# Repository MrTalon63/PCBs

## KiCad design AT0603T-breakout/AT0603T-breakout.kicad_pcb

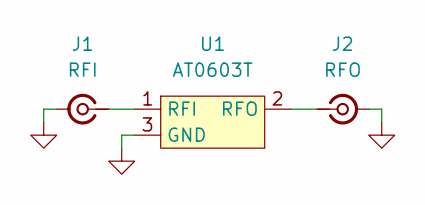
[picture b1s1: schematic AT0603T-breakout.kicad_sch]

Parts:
J1: RFI; SMA_Samtec_SMA-J-P-H-ST-EM1_EdgeMount
J2: RFO; SMA_Samtec_SMA-J-P-H-ST-EM1_EdgeMount
U1: AT0603T

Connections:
GND: J1.2 (Ext), J2.2 (Ext), U1.3 (GND)
unnamed: J1.1 (In), U1.1 (RFI)
unnamed: J2.1 (In), U1.2 (RFO)

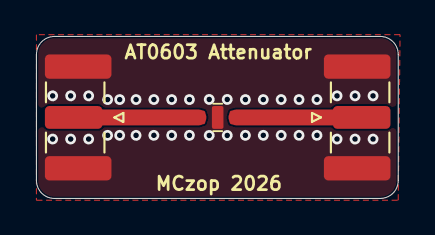
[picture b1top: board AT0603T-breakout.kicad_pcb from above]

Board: 2 copper layers, 20.1 x 9.0 mm, 3 parts (0 on the bottom side), 3 nets.

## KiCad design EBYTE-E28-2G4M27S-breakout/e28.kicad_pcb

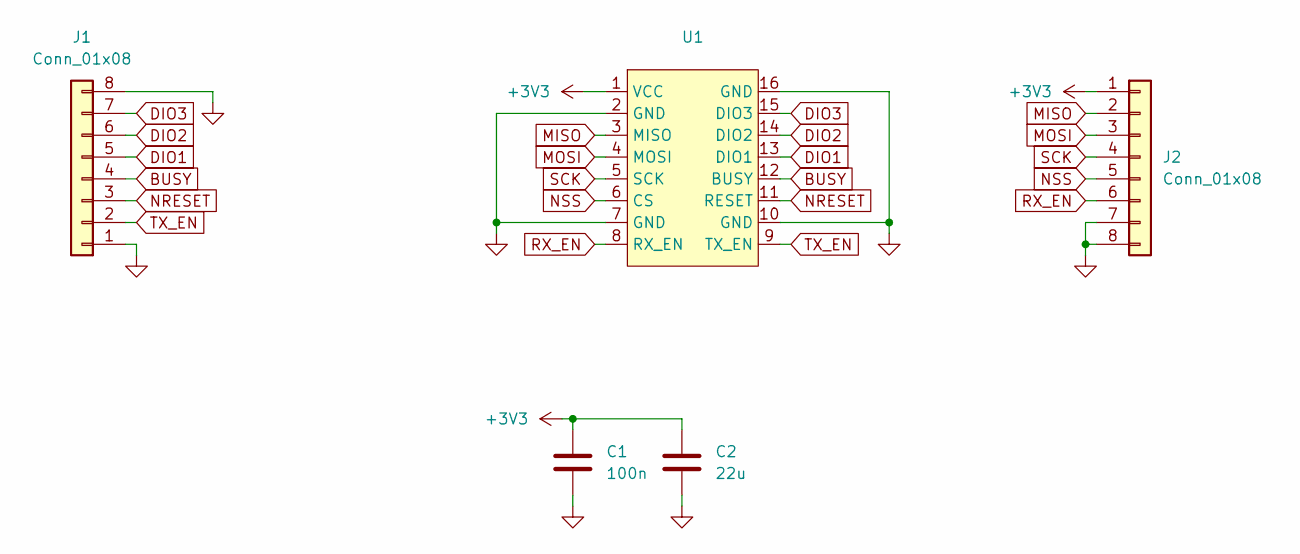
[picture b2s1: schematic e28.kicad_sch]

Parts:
C1: 100n; C_0603_1608Metric_Pad1.08x0.95mm_HandSolder
C2: 22u; C_0603_1608Metric_Pad1.08x0.95mm_HandSolder
J1, J2: Conn_01x08; PinHeader_1x08_P2.54mm_Vertical
U1: E28-2G4M27S

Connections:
+3V3: C1.1, C2.1, J2.1, U1.1 (VCC)
BUSY: J1.4, U1.12 (BUSY)
DIO1: J1.5, U1.13 (DIO1)
DIO2: J1.6, U1.14 (DIO2)
DIO3: J1.7, U1.15 (DIO3)
GND: C1.2, C2.2, J1.1, J1.8, J2.7, J2.8, U1.2 (GND), U1.7 (GND), U1.10 (GND), U1.16 (GND)
MISO: J2.2, U1.3 (MISO)
MOSI: J2.3, U1.4 (MOSI)
NRESET: J1.3, U1.11 (RESET)
NSS: J2.5, U1.6 (CS)
RX_EN: J2.6, U1.8 (RX_EN)
SCK: J2.4, U1.5 (SCK)
TX_EN: J1.2, U1.9 (TX_EN)

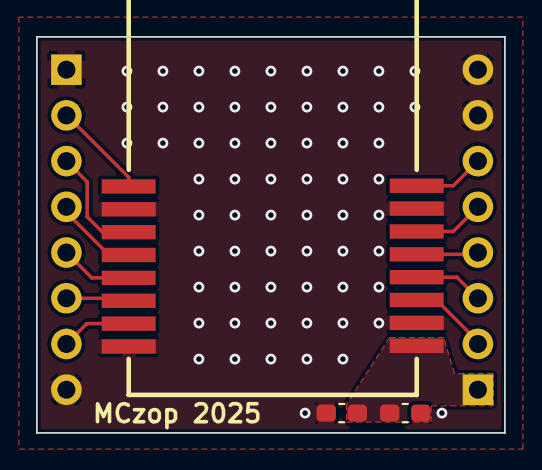
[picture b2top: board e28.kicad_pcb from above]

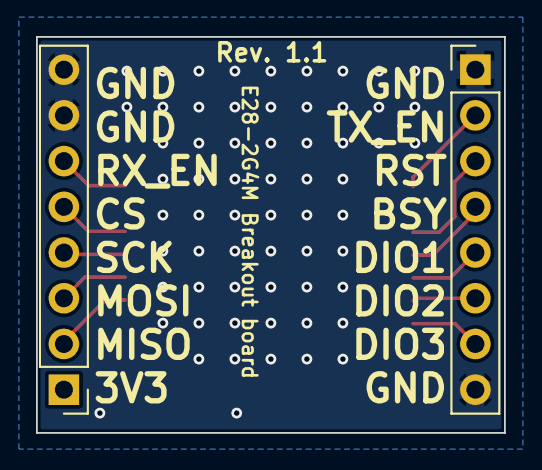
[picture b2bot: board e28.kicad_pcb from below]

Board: 2 copper layers, 26.0 x 22.0 mm, 5 parts (2 on the bottom side), 13 nets.

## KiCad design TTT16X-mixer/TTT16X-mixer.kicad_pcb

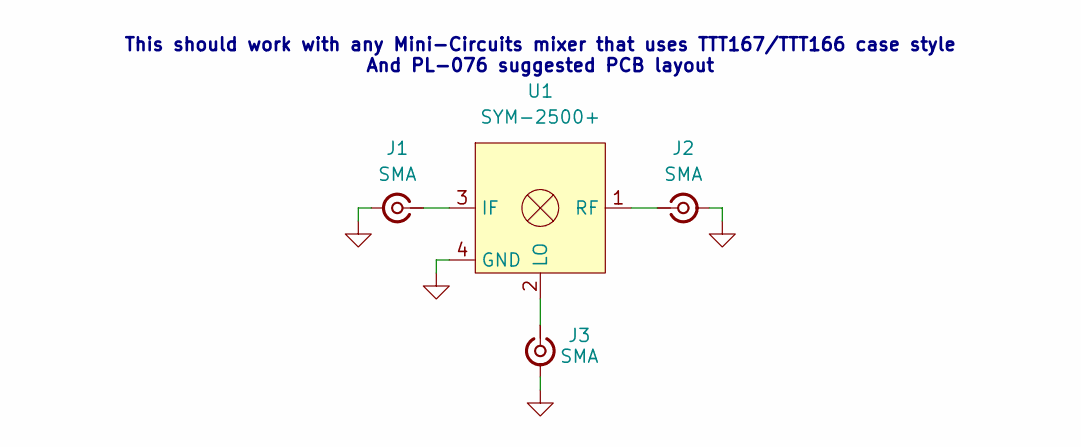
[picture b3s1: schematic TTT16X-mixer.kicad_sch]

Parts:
J1, J2, J3: SMA; SMA_Samtec_SMA-J-P-H-ST-EM1_EdgeMount
U1: SYM-2500+; Mini-Circuits_TTT167_LandPatternPL-079

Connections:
GND: J1.2 (Ext), J2.2 (Ext), J3.2 (Ext), U1.4 (GND)
unnamed: J1.1 (In), U1.3 (IF)
unnamed: J2.1 (In), U1.1 (RF)
unnamed: J3.1 (In), U1.2 (LO)

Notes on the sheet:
This should work with any Mini-Circuits mixer that uses TTT167/TTT166 case style And PL-076 suggested PCB layout

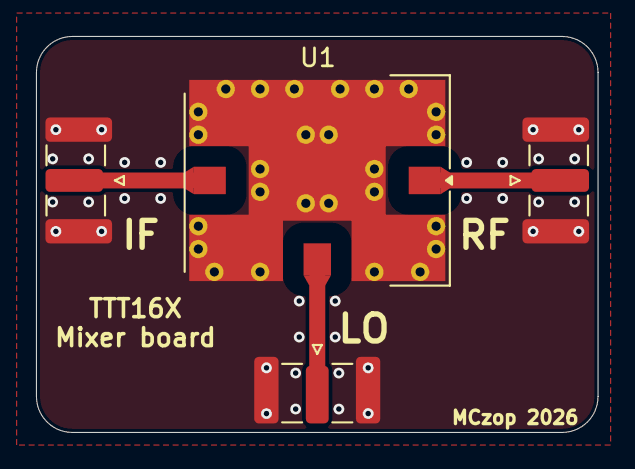
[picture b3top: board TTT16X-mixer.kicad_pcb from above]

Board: 2 copper layers, 31.2 x 22.0 mm, 4 parts (0 on the bottom side), 4 nets.

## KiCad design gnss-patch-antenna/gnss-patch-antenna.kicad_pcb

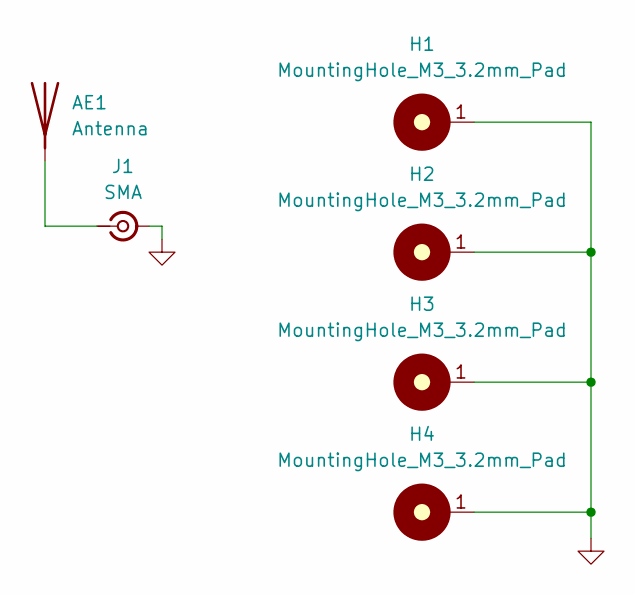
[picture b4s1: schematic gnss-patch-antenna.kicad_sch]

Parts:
AE1: Antenna; Pin_D1.0mm_L10.0mm
H1, H2, H3, H4: MountingHole_M3_3.2mm_Pad; MountingHole_3.2mm_Pad
J1: SMA; SMA_Samtec_SMA-J-P-H-ST-EM1_EdgeMount

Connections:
GND: H1.1, H2.1, H3.1, H4.1, J1.2 (Ext)
unnamed: AE1.1 (A_1), J1.1 (In)

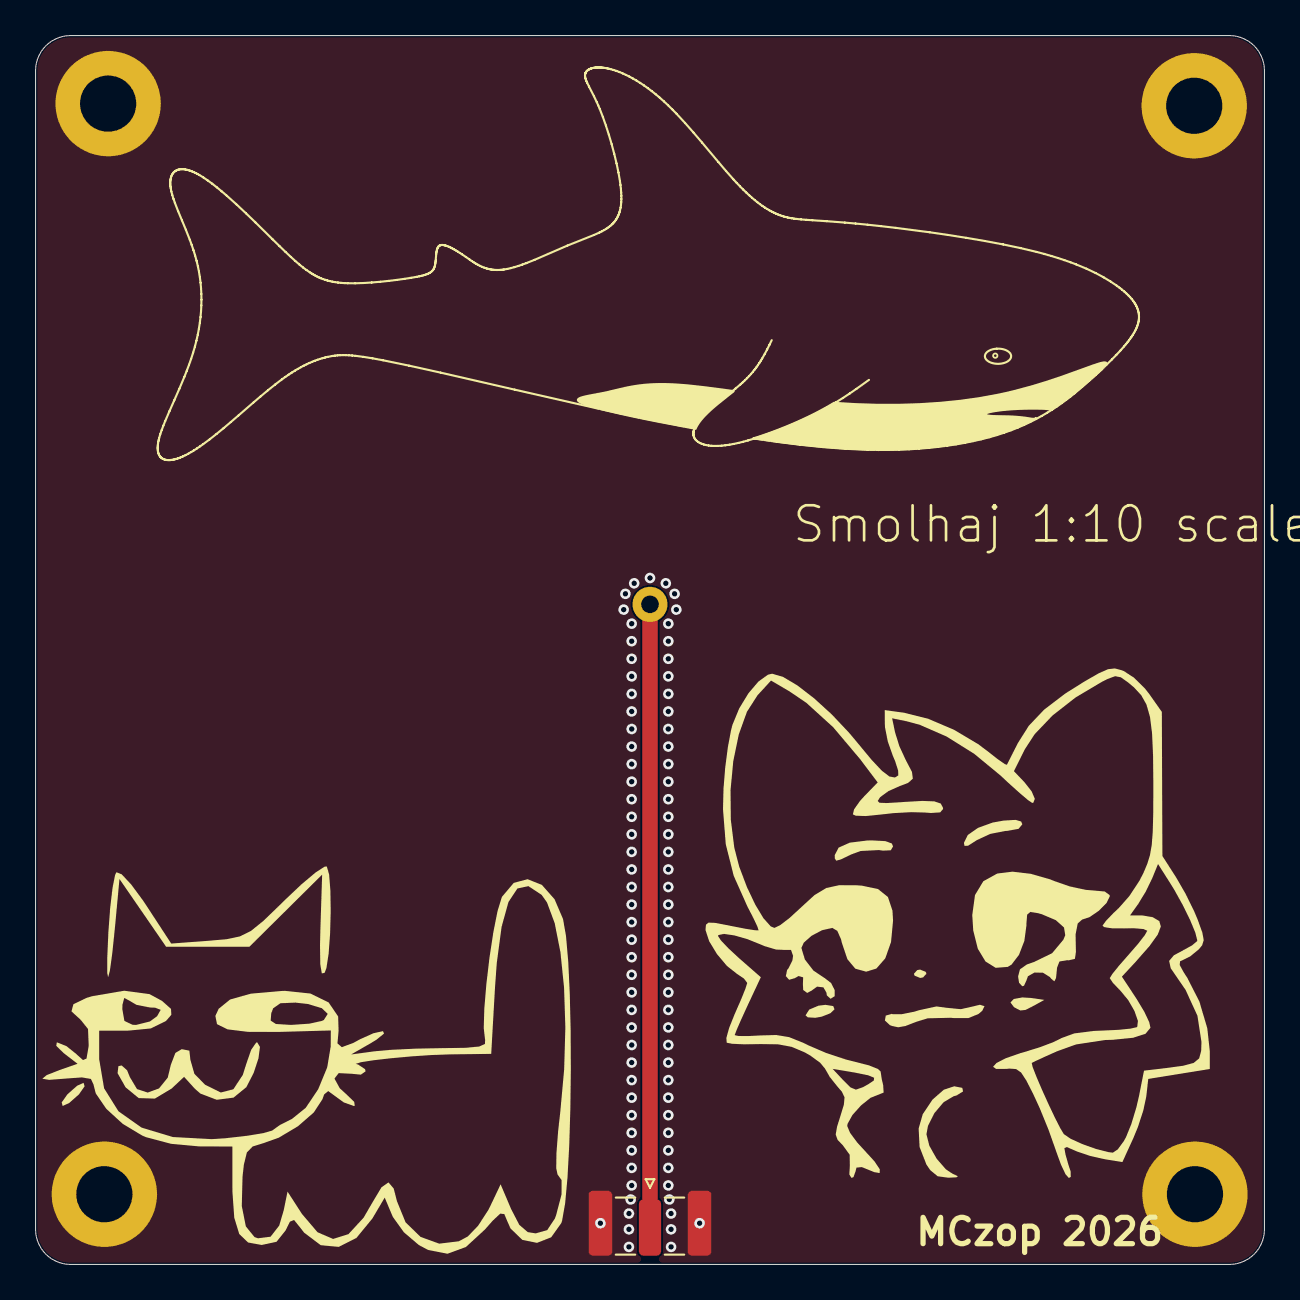
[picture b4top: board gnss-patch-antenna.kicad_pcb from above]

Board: 2 copper layers, 70.0 x 70.0 mm, 6 parts (1 on the bottom side), 2 nets.

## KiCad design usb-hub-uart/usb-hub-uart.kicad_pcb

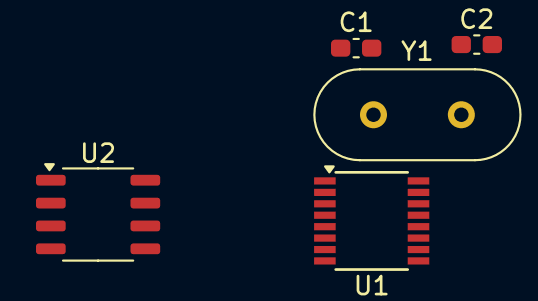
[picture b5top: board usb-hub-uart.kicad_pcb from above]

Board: 2 copper layers, 5 parts (0 on the bottom side), 5 nets, no tracks yet.

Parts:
C1, C2: 15p; C_0603_1608Metric_Pad1.08x0.95mm_HandSolder
U1: SSOP-16_3.9x4.9mm_P0.635mm
U2: CH340N; SOP-8_3.9x4.9mm_P1.27mm
Y1: 12MHz XO; Crystal_HC49-4H_Vertical

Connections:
D1M: U1.7 (DM1), U2.2 (UD-)
D1P: U1.8 (DP1), U2.1 (UD+)
GND: C1.1, C2.1, U1.14 (GND), U2.3 (GND)
unnamed: C2.2, U1.15 (XIN), Y1.2
unnamed: C1.2, U1.16 (XOUT), Y1.1

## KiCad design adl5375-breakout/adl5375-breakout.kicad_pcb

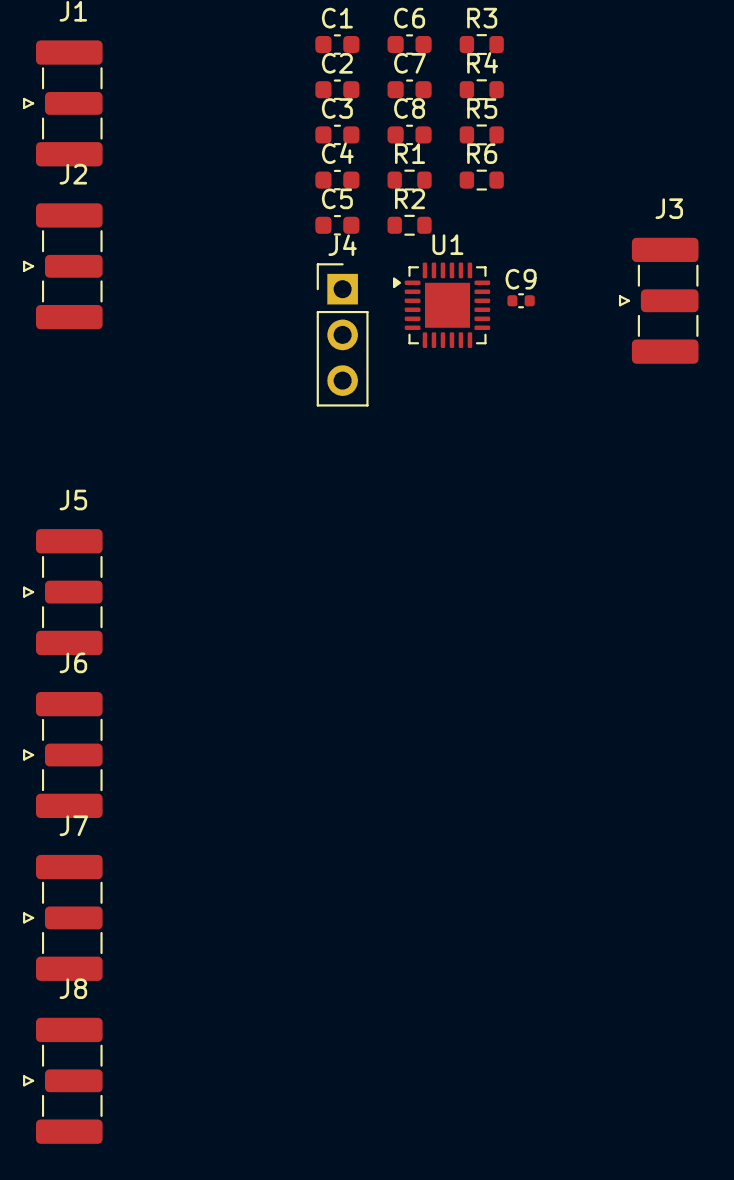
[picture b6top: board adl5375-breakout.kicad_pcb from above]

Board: 2 copper layers, 24 parts (0 on the bottom side), 17 nets, no tracks yet.

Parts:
C1, C2: 100n; C_0603_1608Metric
C3: 1u; C_0603_1608Metric
C4, C5, C6, C7, C8: 100p; C_0603_1608Metric
C9: 100p; C_0402_1005Metric
J1: LOIP; SMA_Samtec_SMA-J-P-H-ST-EM1_EdgeMount
J2: LOIN; SMA_Samtec_SMA-J-P-H-ST-EM1_EdgeMount
J3: RFOUT; SMA_Samtec_SMA-J-P-H-ST-EM1_EdgeMount
J4: DSOP; PinHeader_1x03_P2.54mm_Vertical
J5: IBBN; SMA_Samtec_SMA-J-P-H-ST-EM1_EdgeMount
J6: IBBP; SMA_Samtec_SMA-J-P-H-ST-EM1_EdgeMount
J7: QBBN; SMA_Samtec_SMA-J-P-H-ST-EM1_EdgeMount
J8: QBBP; SMA_Samtec_SMA-J-P-H-ST-EM1_EdgeMount
R1, R2, R3, R4: 0; R_0603_1608Metric
R5, R6: 100; R_0603_1608Metric
U1: ADL5375; LFCSP-24-1EP_4x4mm_P0.5mm_EP2.5x2.5mm

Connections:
+3V3: C1.1, C2.1, C3.1, J4.3, U1.18 (VCC), U1.24 (VCC)
GND: C1.2, C2.2, C3.2, J1.2 (Ext), J2.2 (Ext), J3.2 (Ext), J4.1, J5.2 (Ext), J6.2 (Ext), J7.2 (Ext), J8.2 (Ext), U1.2 (GND), U1.5 (GND), U1.8 (GND), U1.11 (GND), U1.12 (GND), U1.14 (GND), U1.17 (GND), U1.19 (GND), U1.20 (GND), U1.23 (GND), U1.25 (GND)
unnamed: C4.2, C6.1, R2.1
unnamed: C5.2, C6.2, R1.1
unnamed: C7.1, R2.2, R4.1
unnamed: C7.2, R1.2, R3.1
unnamed: C8.1, J1.1 (In), R4.2
unnamed: C8.2, J2.1 (In), R3.2
unnamed: C9.2, J3.1 (In)
unnamed: J4.2, U1.1 (DSOP)
unnamed: J5.1 (In), R5.1, U1.22 (IBBN)
unnamed: J6.1 (In), R5.2, U1.21 (IBBP)
unnamed: J7.1 (In), R6.1, U1.9 (QBBN)
unnamed: J8.1 (In), R6.2, U1.10 (QBBP)
unnamed: C5.1, U1.4 (LOIN)
unnamed: C4.1, U1.3 (LOIP)
unnamed: C9.1, U1.16 (RFOUT)

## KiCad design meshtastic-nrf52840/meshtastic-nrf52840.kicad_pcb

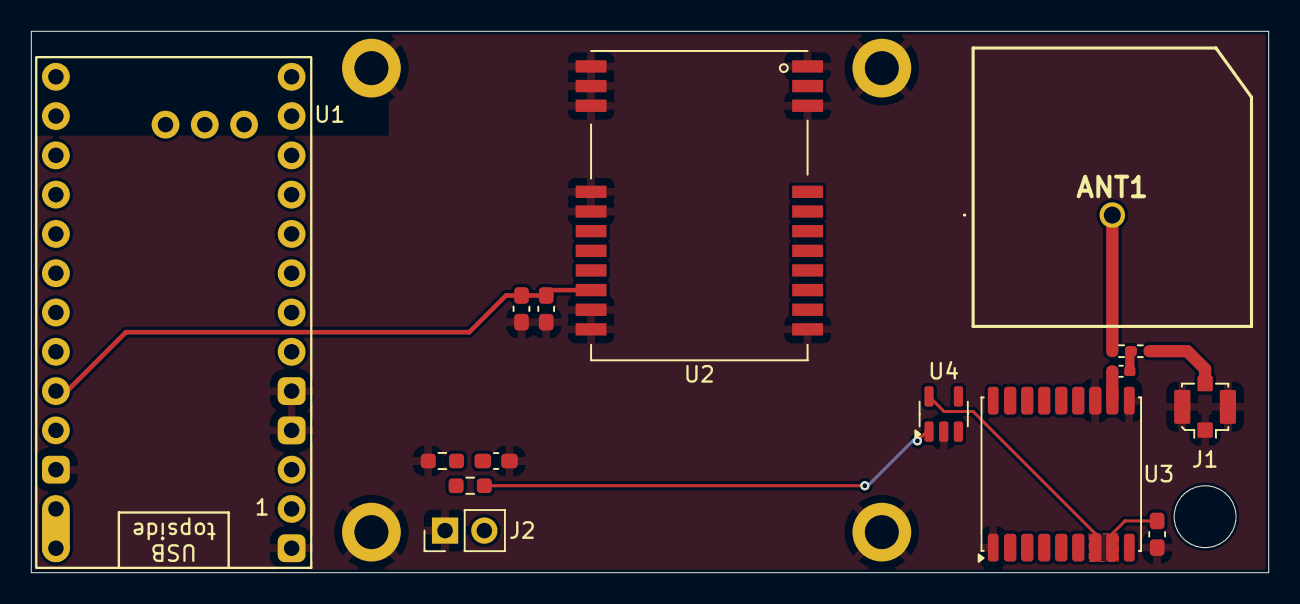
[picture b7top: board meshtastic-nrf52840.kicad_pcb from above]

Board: 2 copper layers, 80.0 x 35.0 mm, 20 parts (0 on the bottom side), 9 nets.

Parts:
ANT1: GPS_PATCH; ANTGNSSCPTH18L1
C1: 47p; C_0402_1005Metric_Pad0.74x0.62mm_HandSolder
C2, C3, C4: 100n; C_0603_1608Metric_Pad1.08x0.95mm_HandSolder
C5: 22u; C_0603_1608Metric_Pad1.08x0.95mm_HandSolder
H1, H2, H3, H4: M2; MountingHole_2.2mm_M2_DIN965_Pad
J1: GNSS_UFL; U.FL_Molex_MCRF_73412-0110_Vertical
J2: VBAT; PinHeader_1x02_P2.54mm_Vertical
R1, R2: 0; R_0402_1005Metric_Pad0.72x0.64mm_HandSolder
R3, R4: 10M; R_0603_1608Metric_Pad0.98x0.95mm_HandSolder
U1: SuperMini nRF52840; SuperMini_nRF52840_AH_USBup
U2: E22-900M22S
U3: MAX-M10S; ublox_MAX
U4: NCP163ASN330T1G; SOT-23-5

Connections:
+3V3: C4.2, C5.2, U1.16 (3V3), U2.9 (VCC)
+BATT: J2.2, R4.1, U1.13 (BAT+), U1.29 (BAT+), U4.1 (VIN)
/BATT_CHRG: C3.1, R3.2, R4.2
GND: C2.1, C3.2, C4.1, C5.1, H1.1, H2.1, H3.1, H4.1, J1.2 (Ext), J2.1, R3.1, U1.3 (GND), U1.4 (GND), U1.14 (GND), U1.28 (GND), U2.1 (GND), U2.2 (GND), U2.3 (GND), U2.4 (GND), U2.5 (GND), U2.10 (GND), U2.11 (GND), U2.12 (GND), U2.20 (GND), U2.22 (GND), U3.1 (GND), U3.10 (GND), U3.12 (GND), U4.2 (GND)
unnamed: ANT1.1, R2.1
unnamed: C1.1, R1.2, R2.2
unnamed: J1.1 (In), R1.1
unnamed: C1.2, U3.11 (RF_IN)
unnamed: C2.2, U3.7 (VCC_IO), U3.8 (VCC), U4.5 (VOUT)

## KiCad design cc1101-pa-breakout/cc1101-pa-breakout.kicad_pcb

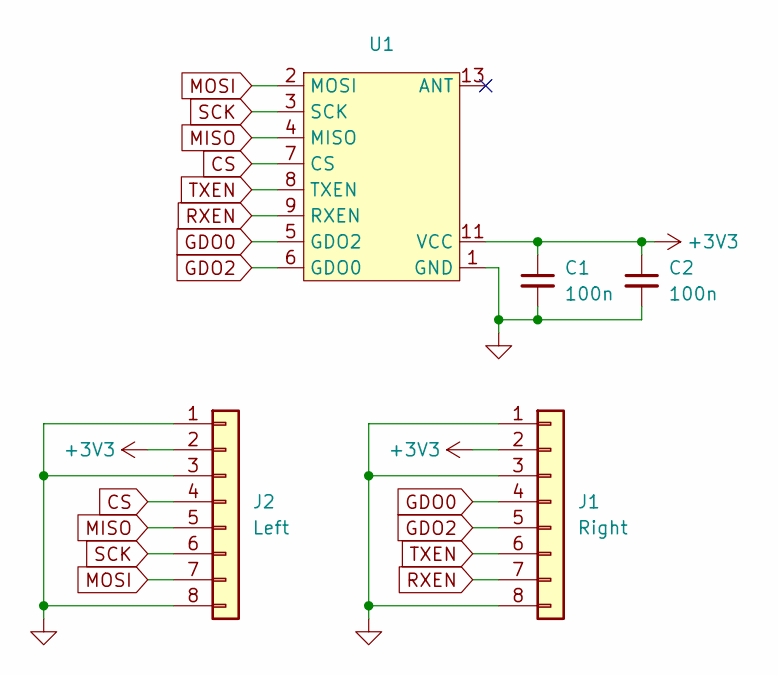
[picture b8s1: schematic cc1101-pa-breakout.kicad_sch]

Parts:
C1, C2: 100n; C_0603_1608Metric_Pad1.08x0.95mm_HandSolder
J1: Right; PinHeader_1x08_P2.54mm_Vertical
J2: Left; PinHeader_1x08_P2.54mm_Vertical
U1: PE07-433M20S

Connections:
+3V3: C1.1, C2.1, J1.2, J2.2, U1.11 (VCC)
CS: J2.4, U1.7 (CS)
GDO0: J1.4, U1.5 (GDO2)
GDO2: J1.5, U1.6 (GDO0)
GND: C1.2, C2.2, J1.1, J1.3, J1.8, J2.1, J2.3, J2.8, U1.1 (GND), U1.12 (GND), U1.14 (GND), U1.15 (GND), U1.16 (GND)
MISO: J2.5, U1.4 (MISO)
MOSI: J2.7, U1.2 (MOSI)
RXEN: J1.7, U1.9 (RXEN)
SCK: J2.6, U1.3 (SCK)
TXEN: J1.6, U1.8 (TXEN)

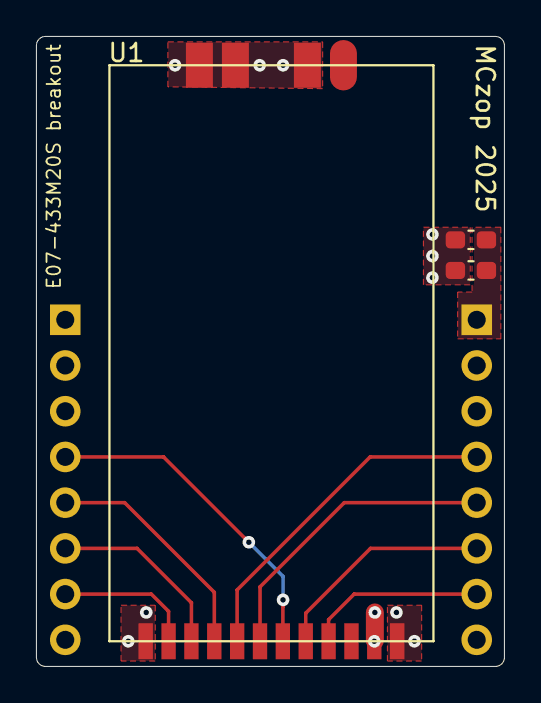
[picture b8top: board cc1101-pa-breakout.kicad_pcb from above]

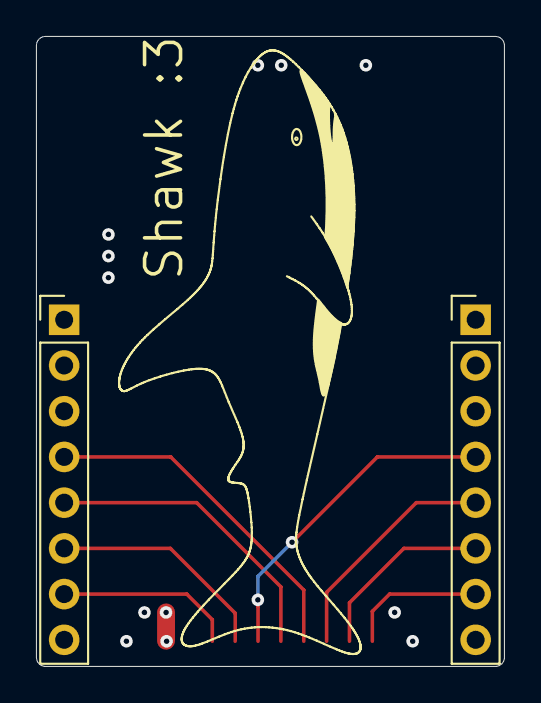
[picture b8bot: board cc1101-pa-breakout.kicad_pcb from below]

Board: 6 copper layers, 26.0 x 35.0 mm, 5 parts (2 on the bottom side), 10 nets.

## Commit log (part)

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2025-05-18 Add E28-2G4M27S/X module breakout
2025-08-20 Fan Controller
2025-08-20 DAN-F10N dongle
2025-09-03 Update gitignore and finish USB GNSS dongle
2025-10-21 SX1255 board
2025-12-24 WS2812B Matrix
2025-12-24 gitignore dumbass
2026-01-05 ughhhh gitignore
2026-03-20 Universal Filter Board
2026-03-20 gitignore
2026-04-07 stuff
2026-04-30 Radio garbage
2026-04-30 Auto stash before merge of "master" and "origin/master"
2026-06-08 rocktrack
2026-06-08 ublox breakout
2026-06-16 stuff 2
